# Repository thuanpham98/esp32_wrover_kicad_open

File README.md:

# ESP-WROVER_OPEN
## Hardware

### Schematic

### PCB Layout

#### Dismention 

#### Top side 

#### Back side 

### 3D

#### Top side 

#### Back side 

### Gerber

# License

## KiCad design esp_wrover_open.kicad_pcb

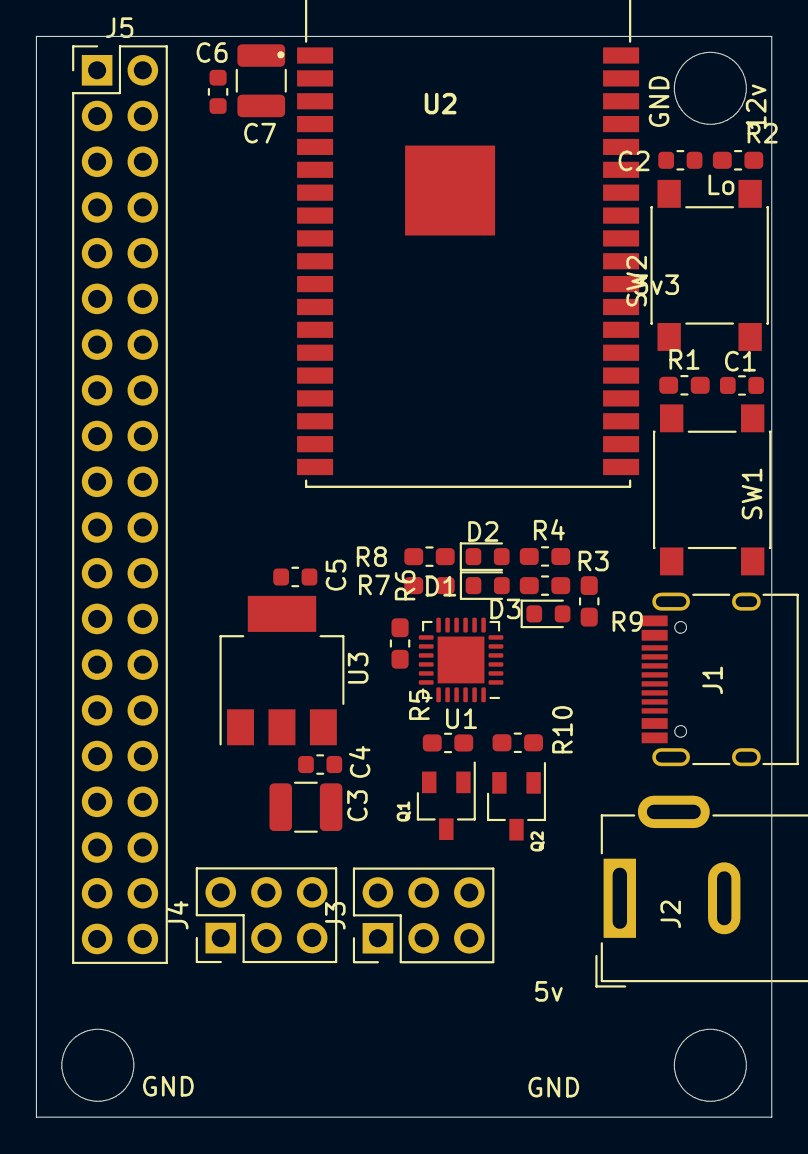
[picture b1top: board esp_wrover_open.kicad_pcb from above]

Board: 2 copper layers, 40.9 x 60.0 mm, 32 parts (0 on the bottom side), 19 nets.

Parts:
C1, C2, C4, C5, C6: 100nF; C_0603_1608Metric
C3: 10uF; R_1210_3225Metric
C7: 10uF; C_1210_3225Metric
D1, D2, D3: LED; LED_0603_1608Metric
J1: USB_C_Receptacle_USB2.0; USB_C_Receptacle_HRO_TYPE-C-31-M-12
J2: Barrel_Jack_Switch; BarrelJack_Wuerth_6941xx301002
J3, J4: Conn_02x03_Counter_Clockwise; PinHeader_2x03_P2.54mm_Vertical
J5: Conn_02x20_Counter_Clockwise; PinHeader_2x20_P2.54mm_Vertical
Q1, Q2: Q_NPN_BCE; SOT-23_standar
R1, R2, R5, R6, R10: 10K; R_0603_1608Metric_Pad1.05x0.95mm_HandSolder
R3, R4, R7, R8: 470; R_0603_1608Metric_Pad1.05x0.95mm_HandSolder
R9: R; R_0603_1608Metric_Pad1.05x0.95mm_HandSolder
SW1: reset; SW_Push_1P1T_NO_6x6mm_H9.5mm
SW2: boot; SW_Push_1P1T_NO_6x6mm_H9.5mm
U1: CP2104; QFN-24-1EP_4x4mm_P0.5mm_EP2.6x2.6mm
U2: ESP32-WROVER-B_(16MB); XCVR_ESP32-WROVER-B_(16MB)
U3: AMS1117-3.3; SOT-223-3_TabPin2

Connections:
+3V3: C5.1, C6.2, C7.2, J4.1, J4.3, J4.5, J5.5, J5.13, J5.39, R1.1, R2.1, R3.1, R4.1, R9.2, U2.2, U3.2
+5V: C3.1, C4.1, J1.A4, J1.A9, J1.B4, J1.B9, J2.1, J3.1, J3.3, J3.5, J5.4, J5.40, U1.7, U1.8, U3.3
DTR: Q1.3, R10.1, U1.23
EN: C1.1, J5.1, Q2.2, R1.2, SW1.1
GND: C1.2, C2.2, C3.2, C4.2, C5.2, C6.1, C7.1, D3.1, J1.A1, J1.A12, J1.B1, J1.B12, J1.S1, J2.2, J2.3, J3.2, J3.4, J3.6, J4.2, J4.4, J4.6, J5.6, J5.14, J5.37, J5.38, R6.2, SW1.2, SW2.2, U1.2, U1.25, U2.1, U2.15, U2.38, U2.39, U3.1
IO0: C2.1, Q1.2, R2.2, SW2.1
unnamed: D1.2, R3.2
unnamed: D2.2, R4.2
unnamed: D3.2, R9.1
unnamed: J1.A6, J1.B6, U1.3
unnamed: J1.A7, J1.B7, U1.4
unnamed: Q1.1, R5.2
unnamed: Q2.1, R10.2
unnamed: R7.2, U1.21
unnamed: R8.2, U1.20
RTS: Q2.3, R5.1, U1.19
RX0: D1.1, J5.2, R7.1
SU-: R6.1, U1.15
TX0: D2.1, J5.3, R8.1

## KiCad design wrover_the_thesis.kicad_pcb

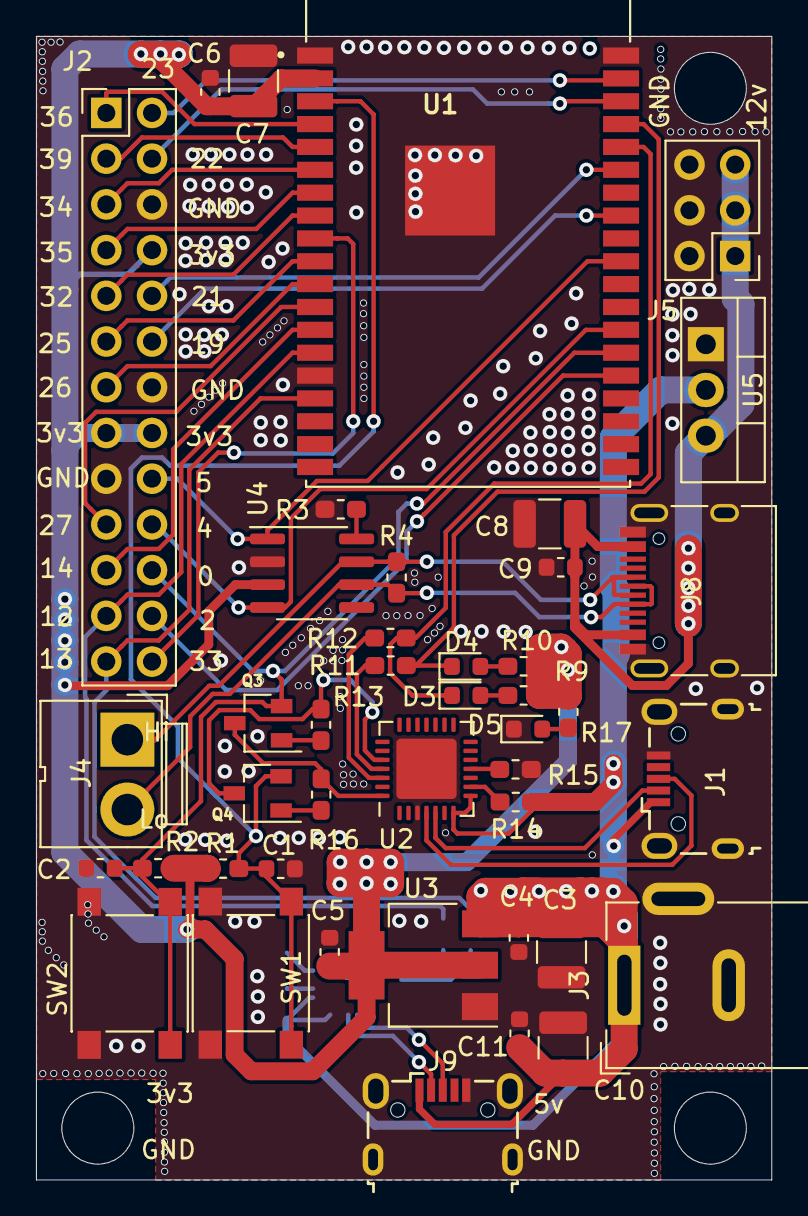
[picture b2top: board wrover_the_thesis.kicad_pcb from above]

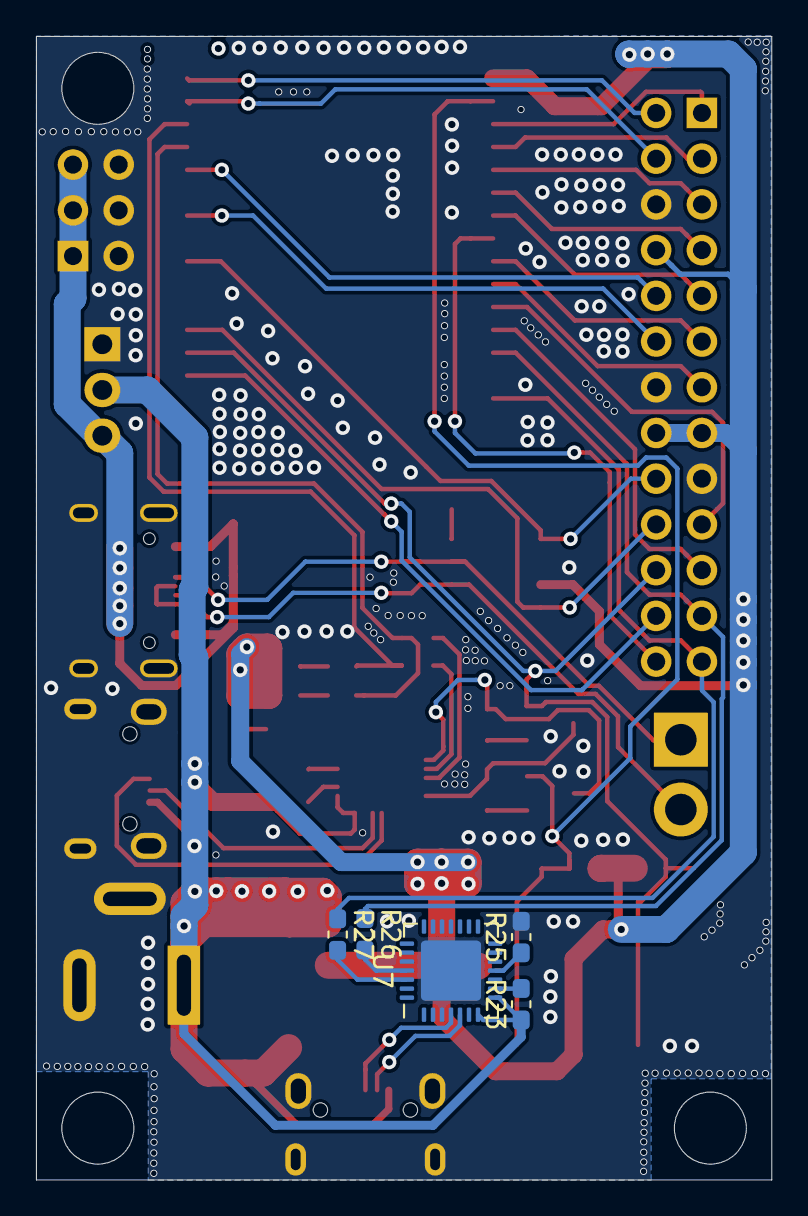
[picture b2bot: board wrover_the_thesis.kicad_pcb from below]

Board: 2 copper layers, 40.9 x 63.5 mm, 48 parts (5 on the bottom side), 49 nets.

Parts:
C1, C2, C4, C5, C6, C9, C11: 100nF; C_0603_1608Metric
C3, C8, C10: 10uF; R_1210_3225Metric
C7: 10uF; C_1210_3225Metric
D3, D4, D5: LED; LED_0603_1608Metric
J1, J9: USB_B_Micro; USB_Micro-B_Wuerth_629105150521
J2: Conn_02x13_Counter_Clockwise; PinHeader_2x13_P2.54mm_Vertical
J3: Barrel_Jack_Switch; BarrelJack_Wuerth_6941xx301002
J4: CAN_out; JWT_A3963_1x02_P3.96mm_Vertical
J5: Conn_02x03_Counter_Clockwise; PinHeader_2x03_P2.54mm_Vertical
J8: USB_C_Receptacle_USB2.0; USB_C_Receptacle_HRO_TYPE-C-31-M-12
Q3, Q4: Q_NPN_BCE; SOT-23_standar
R1, R2, R3, R13, R15, R16, R25: 10K; R_0603_1608Metric_Pad1.05x0.95mm_HandSolder
R4: 120; R_0603_1608Metric_Pad1.05x0.95mm_HandSolder
R9, R10, R11, R12, R26, R27: 470; R_0603_1608Metric_Pad1.05x0.95mm_HandSolder
R14, R23: 1K; R_0603_1608Metric_Pad1.05x0.95mm_HandSolder
R17: R; R_0603_1608Metric_Pad1.05x0.95mm_HandSolder
SW1: reset; SW_Push_1P1T_NO_6x6mm_H9.5mm
SW2: boot; SW_Push_1P1T_NO_6x6mm_H9.5mm
U1: ESP32-WROVER-B_(16MB); XCVR_ESP32-WROVER-B_(16MB)
U2, U7: CP2102N; QFN-28-1EP_5x5mm_P0.5mm_EP3.35x3.35mm
U3: AMS1117-3.3; SOT-223-3_TabPin2
U4: SN65HVD230; SOIC-8_3.9x4.9mm_P1.27mm
U5: LM1084-5.0; TO-220-3_Vertical

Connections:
+3V3: C5.1, C6.2, C7.2, J2.8, J2.15, J2.16, R1.1, R2.1, R9.1, R10.1, R17.2, U1.2, U3.2, U4.3
+5V: C3.1, C4.1, C10.1, C11.1, J1.1, J3.1, J9.1, R14.1, R23.1, U2.7, U2.8, U3.3, U5.2, U7.7, U7.8
+12V: C8.1, C9.1, J5.1, J5.3, J5.5, J8.A4, J8.A9, J8.B4, J8.B9, U5.3
AN0: J2.1, U1.4
AN3: J2.3, U1.5
AN4: J2.9, U1.8
AN5: J2.26, U1.9
AN6: J2.5, U1.6
AN7: J2.7, U1.7
CAN_H: J4.1, J8.A6, J8.B6, R4.1, U4.7
CAN_L: J4.2, J8.A7, J8.B7, R4.2, U4.6
CAN_RX: J2.20, U1.26, U4.4
CAN_TX: J2.18, U1.29, U4.1
DAC1: J2.11, U1.10
DAC2: J2.13, U1.11
DTR: Q3.3, R16.1, U2.28
EN: C1.1, Q4.2, R1.2, SW1.1, U1.3
GND: C1.2, C2.2, C3.2, C4.2, C5.2, C6.1, C7.1, C8.2, C9.2, C10.2, C11.2, D5.1, J1.5, J1.6, J2.6, J2.14, J2.17, J3.2, J3.3, J5.2, J5.4, J5.6, J8.A1, J8.A12, J8.B1, J8.B12, J8.S1, J9.5, J9.6, R3.2, R15.2, R25.2, SW1.2, SW2.2, U1.1, U1.15, U1.38, U1.39, U2.3, U2.29, U3.1, U4.2, U5.1, U7.3, U7.29
HSPI_CLK: J2.21, U1.13
HSPI_MISO: J2.23, R26.1, U1.14
HSPI_MOSI: J2.25, R27.1, U1.16
HSPI_SE: J2.19, U1.12
I2C_F_C: J2.2, U1.37
I2C_F_D: J2.4, U1.36
I2C_S_C: J2.10, U1.33
I2C_S_D: J2.12, U1.31
IO0: C2.1, J2.22, Q3.2, R2.2, SW2.1, U1.25
IO2: J2.24, U1.24
unnamed: D3.2, R9.2
unnamed: D4.2, R10.2
unnamed: D5.2, R17.1
unnamed: J1.2, U2.5
unnamed: J1.3, U2.4
unnamed: J9.2, U7.5
unnamed: J9.3, U7.4
unnamed: Q3.1, R13.2
unnamed: Q4.1, R16.2
unnamed: R3.1, U4.8
unnamed: R11.2, U2.25
unnamed: R12.2, U2.26
unnamed: R14.2, U2.9
unnamed: R23.2, U7.9
unnamed: R25.1, U7.11
unnamed: R26.2, U7.25
unnamed: R27.2, U7.26
RTS: Q4.3, R13.1, U2.24
RX0: D3.1, R12.1, U1.34
SU-: R15.1, U2.11
TX0: D4.1, R11.1, U1.35

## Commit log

2021-05-05 init
2021-05-14 cpmonent
